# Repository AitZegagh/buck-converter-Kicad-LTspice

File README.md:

# 12 V to 3.3 V Buck Converter

A 12 V to 3.3 V, 2A buck converter, designed in three steps. 
I started by researching how a buck converter works, and moved on to the hand calculations (duty cycle, inductor, output capacitor)
I then simulated it in LTspice, going from a simple diode version to a synchronous one with real MOSFETs. 
I then designed the schematic and PCB in KiCad around the TI TPS54202 regulator.

## Files

- `ltspice/Buck_ideal.asc`: buck with ideal switches
- `ltspice/Buck_real.asc`: same circuit with real MOSFETs
- `kicad/Buck.pro`: KiCad project (open this one)
- `kicad/Buck.sch`: schematic
- `kicad/Buck.kicad_pcb`: PCB layout

## Hand calculations

**Specifications:** Vin = 12 V, Vout = 3.3 V, Iout = 2A, fsw = 500kHz, output ripple ≤ 0.5 % of Vout (16.5 mV).

**Duty cycle**

D = Vout / Vin = 3.3 / 12 = 0.275

**Inductor**

I chose an inductor ripple current of ΔIL = 0.6 A (30 % of the 2 A load):

L = Vout · (1 − D) / (ΔIL · fsw) = 3.3 × 0.725 / (0.6 × 500 kHz) ≈ 8 µH

**Output capacitor**

Cout ≥ ΔIL / (8 · fsw · ΔVout) = 0.6 / (8 × 500 kHz × 16.5 mV) ≈ 9.1 µF

**Load resistor (for the simulation)**

Rload = Vout / Iout = 3.3 / 2 = 1.65 Ω

## LTspice simulation

### Normal diode

First version: switch S1, a normal diode, L = 10 µH, C = 22 µF and a 1.65 Ω load. Vin is 12 V and the switch is driven at 500 kHz.

Waveforms of Vin, Vout and the inductor current IL:

The output is only **2.69 V** instead of 3.3 V, because the diode voltage drop is too high.

### Schottky diode

I researched how to reduce the drop and replaced the diode with a Schottky (1N5819). The output improved to **2.96 V**.

### Adjusting the duty cycle

To get back to 3.3 V, I redid the duty cycle estimate with the diode drop (about 0.47 V):

3.3 = 12 × D − (1 − D) × 0.47, so D ≈ 0.30 and Ton ≈ 605 ns

This gives **3.29 V**.

The diode still wastes about 0.6 W (0.47 V × 1.3 A average diode current), roughly 10 % of the output power.

### Synchronous version (second switch)

To reduce the loss further, I replaced the diode's job with a second switch S2 in parallel with it.

- When S1 opens, the inductor current has to keep flowing, and it needs a path to ground. That path used to be the diode.
- With S2 closed during the off-time, the current flows through S2 instead.
- Diode path: 0.47 V × 1.3 A ≈ 0.6 W
- S2 path: about 2² × 0.02 Ω × 0.7 ≈ 0.06 W

S1 and S2 must never be on at the same time, otherwise they short Vin to ground. So I added a **20 ns dead time** between them. The diode stays in parallel to carry the current during these short gaps.

Results:

### Summary 

| | Normal diode | Schottky | Schottky, Ton = 605 ns | Synchronous |
|---|---|---|---|---|
| Average Vout | 2.69 V | 2.96 V | 3.29 V | 3.28 V |
| Ripple | 5.8 mV | 8.7 mV | 7.5 mV | 6.4 mV |
| Efficiency | **81.5 %** | **89.6 %** | **90.6 %** | **99.2 %** |

We now have a working simulation with a good efficiency (**99.2 %**).
However, this is still the ideal case, with perfect switches, so this number is sure to drop with real components.

### Real MOSFETs (N-channel)

Next, I replaced the ideal switches with real N-channel MOSFETs (Si7336ADP). The Schottky diode stays in parallel to carry the current during the dead time.

**Why N-channel:** an NMOS has a lower Rds(on) than a PMOS of the same size, so it wastes less power. The catch is that the high-side NMOS (M1) needs its gate voltage to be higher than its source, and its source is the switch node, which jumps between 0 V and 12 V. So the gate source V2 is placed between the gate and the switch node. It gives a 5 V gate-to-source voltage whatever the switch node does. The low-side MOSFET (M2) has its source on ground, so its gate source is simply referenced to ground.

Results:

| | Ideal switches | Real MOSFETs |
|---|---|---|
| Average Vout | 3.285 V | 3.295 V |
| Ripple | 6.4 mV | 5.6 mV |
| Pin | 6.59 W | 6.83 W |
| Pout | 6.54 W | 6.58 W |
| Efficiency | 99.2 % | **96.4 %** |

As expected, the efficiency dropped. This is due to the internal resistance of the MOSFETS and the MOSFET capacitances

The output voltage and ripple stay on target, so the design still works with real components.

## KiCad schematic and PCB

For the board I used the TI **TPS54202** (4.5–28 V input, 2 A, fixed 500 kHz). It has the high-side and low-side switches built in (148 mΩ and 78 mΩ), so the two MOSFETs and their gate drive from the simulation are replaced by a single chip. The simulation still tells me what to expect: a synchronous buck at 500 kHz with real MOSFET resistances.

### Choosing the components

I took the component values from the datasheet.

**Output voltage divider.** The output voltage is set by two resistors from Vout to the FB pin (datasheet section 6.3.8), with a 100 kΩ upper resistor as recommended:

Vout = Vref × (1 + R_top / R_bottom), with Vref = 0.596 V

For 3.3 V, the datasheet gives R_top = 100 kΩ and R_bottom = 22.1 kΩ:

Vout = 0.596 × (1 + 100 / 22.1) = 3.29 V

**Other components.** Table 7-2 of the datasheet gives the recommended values for 3.3 V:

| Part | Value | Role |
|---|---|---|
| L1 | 10 µH | Inductor, gives about 0.48 A of ripple current |
| Cout1 + Cout2 | 2 × 22 µF = 44 µF | Output capacitor, keeps the ripple low |
| C1 | 56 pF | Across the upper divider resistor, helps the loop stability |
| Cboot | 0.1 µF | Between BOOT and SW, powers the gate drive of the high-side switch (same floating-gate problem as in the simulation) |
| Cin | 10 µF | Input capacitor, supplies the pulsed input current |

### Schematic

### PCB

I placed the parts around the TPS54202 and routed a two-layer board.
The bottom layer is a solid ground plane, connected to the GND pads through vias. The board outline is drawn on the Edge.
Cuts layer, and the design passes the KiCad design rule check (DRC) with no errors.

Layout choices, following the datasheet's layout guidelines:

- The input capacitor (Cin) and the bootstrap capacitor (Cboot) sit right next to the IC, and the switch-node trace between U1 and L1 is kept short.
- The output capacitors are placed right after the inductor.
- The feedback divider (R1, R2, C1) is placed away from the switch node and takes its voltage from the output, so the switching noise does not disturb the FB pin.

3D views:

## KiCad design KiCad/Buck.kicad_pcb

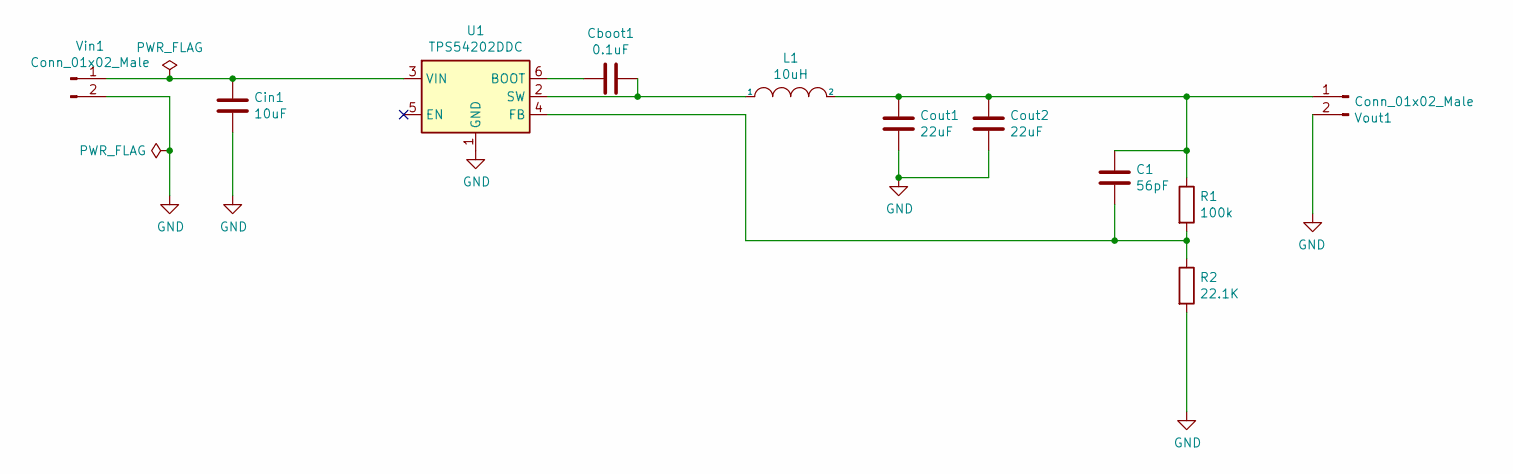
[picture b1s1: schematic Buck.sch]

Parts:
C1: 56pF; C_0603_1608Metric_Pad1.08x0.95mm_HandSolder
Cboot1: 0.1uF; C_0603_1608Metric_Pad1.08x0.95mm_HandSolder
Cin1: 10uF; C_0805_2012Metric_Pad1.18x1.45mm_HandSolder
Cout1, Cout2: 22uF; C_1206_3216Metric_Pad1.33x1.80mm_HandSolder
L1: 10uH; L_Bourns_SRN6045TA; MPN SRN6045TA-100M
R1: 100k; R_0805_2012Metric_Pad1.20x1.40mm_HandSolder
R2: 22.1K; R_0805_2012Metric_Pad1.20x1.40mm_HandSolder
U1: TPS54202DDC; SOT-23-6
Vin1: Conn_01x02_Male; PinHeader_1x02_P2.54mm_Vertical
Vout1: Conn_01x02_Male; PinHeader_1x02_P2.54mm_Vertical

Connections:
GND: Cin1.2, Cout1.2, Cout2.2, R2.2, U1.1 (GND), Vin1.2, Vout1.2
unnamed: C1.1, Cout1.1, Cout2.1, L1.2, R1.1, Vout1.1
unnamed: C1.2, R1.2, R2.1, U1.4 (FB)
unnamed: Cboot1.1, U1.6 (BOOT)
unnamed: Cboot1.2, L1.1, U1.2 (SW)
unnamed: Cin1.1, U1.3 (VIN), Vin1.1

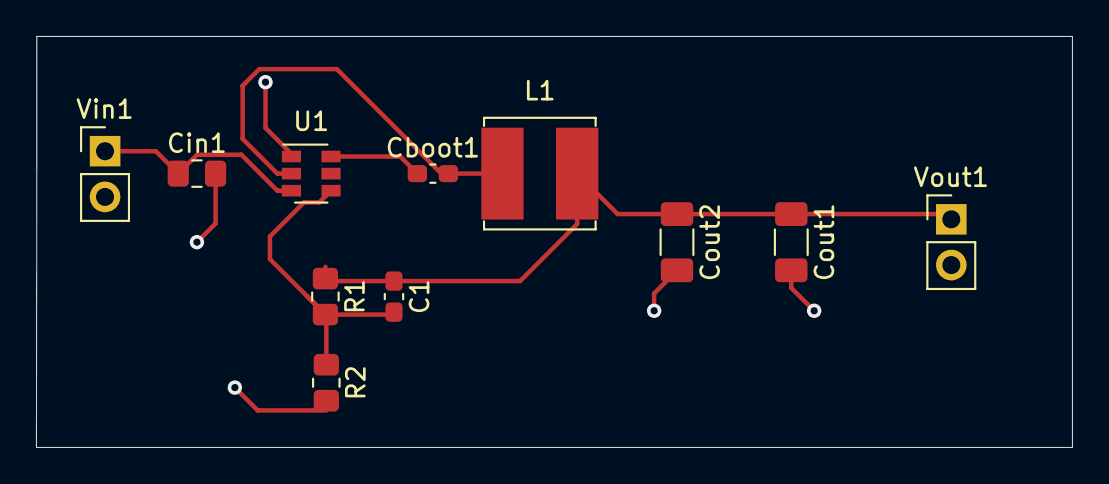
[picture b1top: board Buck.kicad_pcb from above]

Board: 2 copper layers, 57.6 x 22.8 mm, 11 parts (0 on the bottom side), 6 nets.
